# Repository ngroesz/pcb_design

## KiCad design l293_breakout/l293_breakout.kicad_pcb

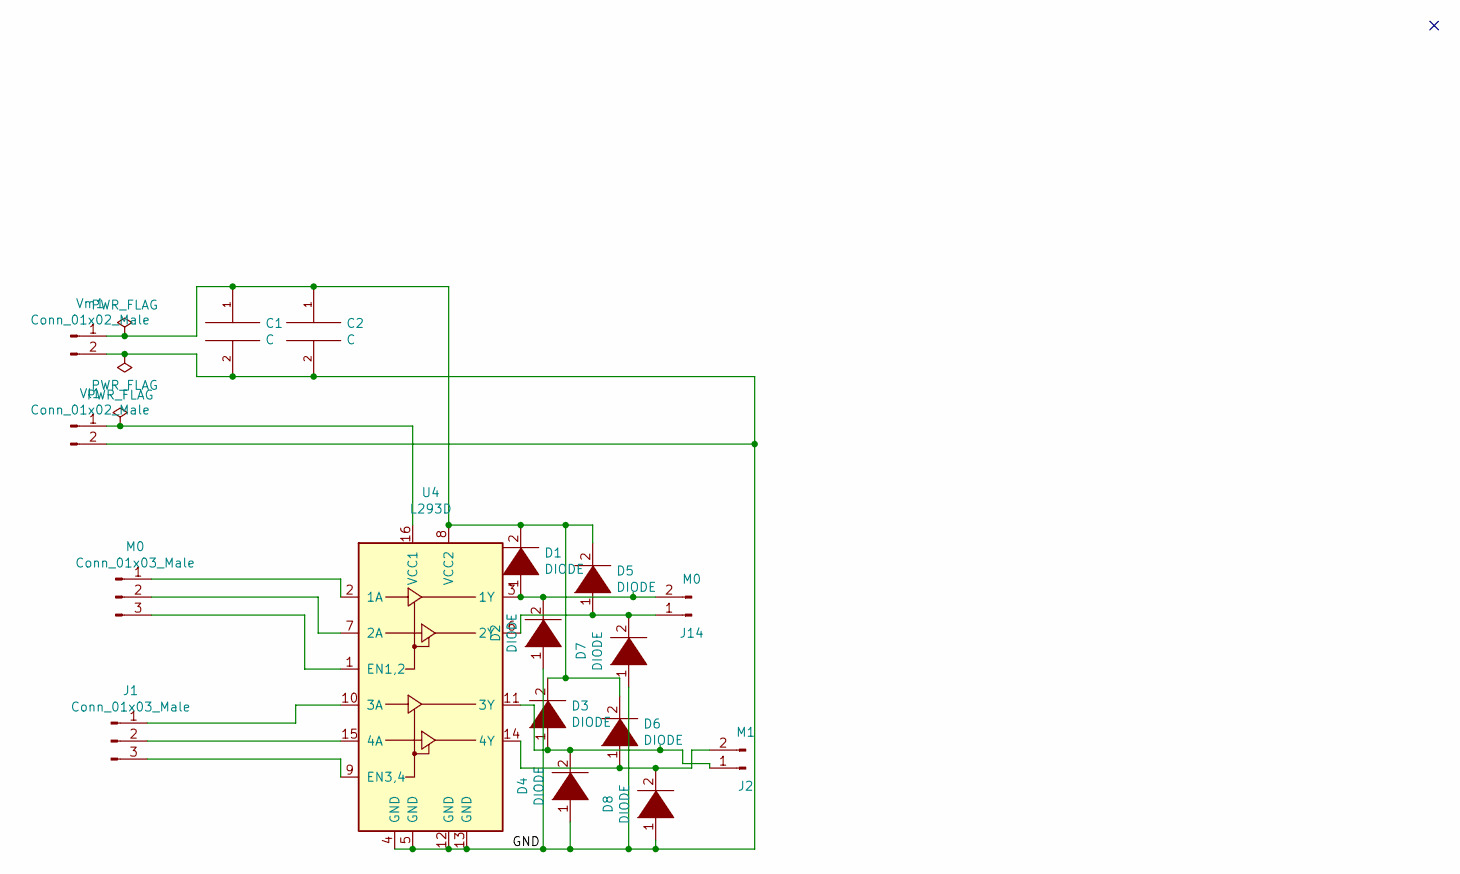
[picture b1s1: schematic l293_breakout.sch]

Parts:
C1: C; C_Disc_D4.7mm_W2.5mm_P5.00mm
C2: C; CP_Radial_D4.0mm_P2.00mm
D1, D2, D3, D4, D5, D6, D7, D8: DIODE; D_A-405_P7.62mm_Horizontal
J1: Conn_01x03_Male; JST_EH_B3B-EH-A_1x03_P2.50mm_Vertical
J2: M1; JST_EH_B2B-EH-A_1x02_P2.50mm_Vertical
J14: M0; JST_EH_B2B-EH-A_1x02_P2.50mm_Vertical
M0: Conn_01x03_Male; JST_EH_B3B-EH-A_1x03_P2.50mm_Vertical
U4: L293D; DIP-16_W7.62mm
Vl1: Conn_01x02_Male; JST_EH_B2B-EH-A_1x02_P2.50mm_Vertical
Vm1: Conn_01x02_Male; JST_EH_B2B-EH-A_1x02_P2.50mm_Vertical

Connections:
/GND: C1.2, C2.2, D2.1 (K), D4.1 (K), D7.1 (K), D8.1 (K), U4.4 (GND), U4.5 (GND), U4.12 (GND), U4.13 (GND), Vl1.2, Vm1.2
unnamed: C1.1, C2.1, D1.2 (A), D3.2 (A), D5.2 (A), D6.2 (A), U4.8 (VCC2), Vm1.1
unnamed: D1.1 (K), D2.2 (A), J14.2, U4.3 (1Y)
unnamed: D3.1 (K), D4.2 (A), J2.1, U4.11 (3Y)
unnamed: D5.1 (K), D7.2 (A), J14.1, U4.6 (2Y)
unnamed: D6.1 (K), D8.2 (A), J2.2, U4.14 (4Y)
unnamed: J1.1, U4.10 (3A)
unnamed: J1.2, U4.15 (4A)
unnamed: J1.3, U4.9 (EN3,4)
unnamed: M0.1, U4.2 (1A)
unnamed: M0.2, U4.7 (2A)
unnamed: M0.3, U4.1 (EN1,2)
unnamed: U4.16 (VCC1), Vl1.1

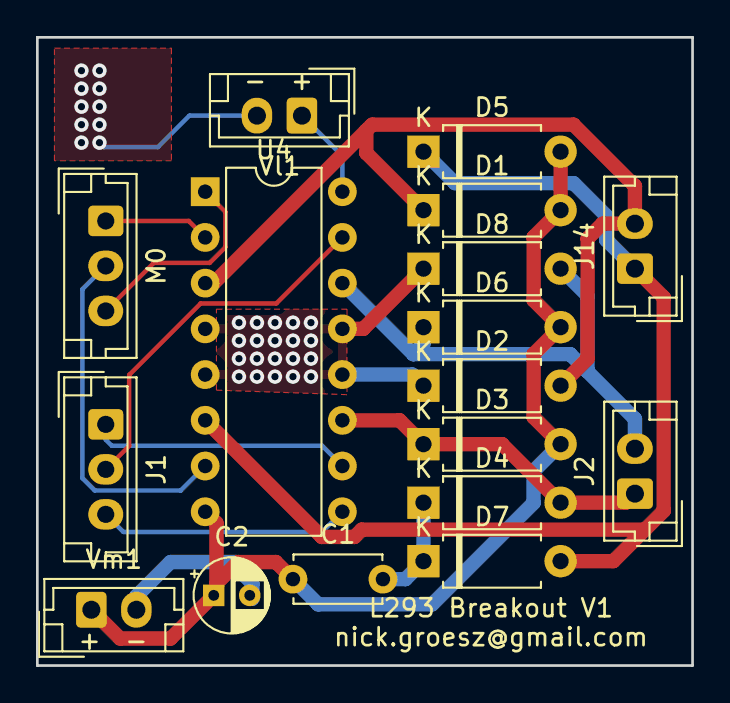
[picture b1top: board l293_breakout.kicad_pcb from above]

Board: 2 copper layers, 36.4 x 34.9 mm, 17 parts (0 on the bottom side), 13 nets.

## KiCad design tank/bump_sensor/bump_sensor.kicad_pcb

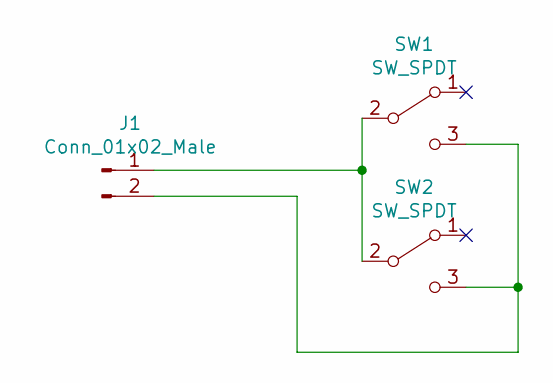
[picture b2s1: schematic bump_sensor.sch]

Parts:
J1: Conn_01x02_Male; JST_EH_B2B-EH-A_1x02_P2.50mm_Vertical
SW1, SW2: SW_SPDT; micro_switch

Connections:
unnamed: J1.1, SW1.2 (B), SW2.2 (B)
unnamed: J1.2, SW1.3 (C), SW2.3 (C)

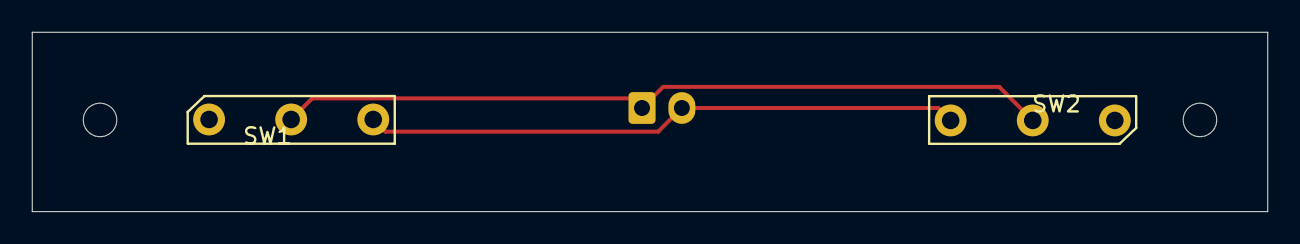
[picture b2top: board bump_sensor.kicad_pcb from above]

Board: 2 copper layers, 77.5 x 11.2 mm, 3 parts (1 on the bottom side), 2 nets.

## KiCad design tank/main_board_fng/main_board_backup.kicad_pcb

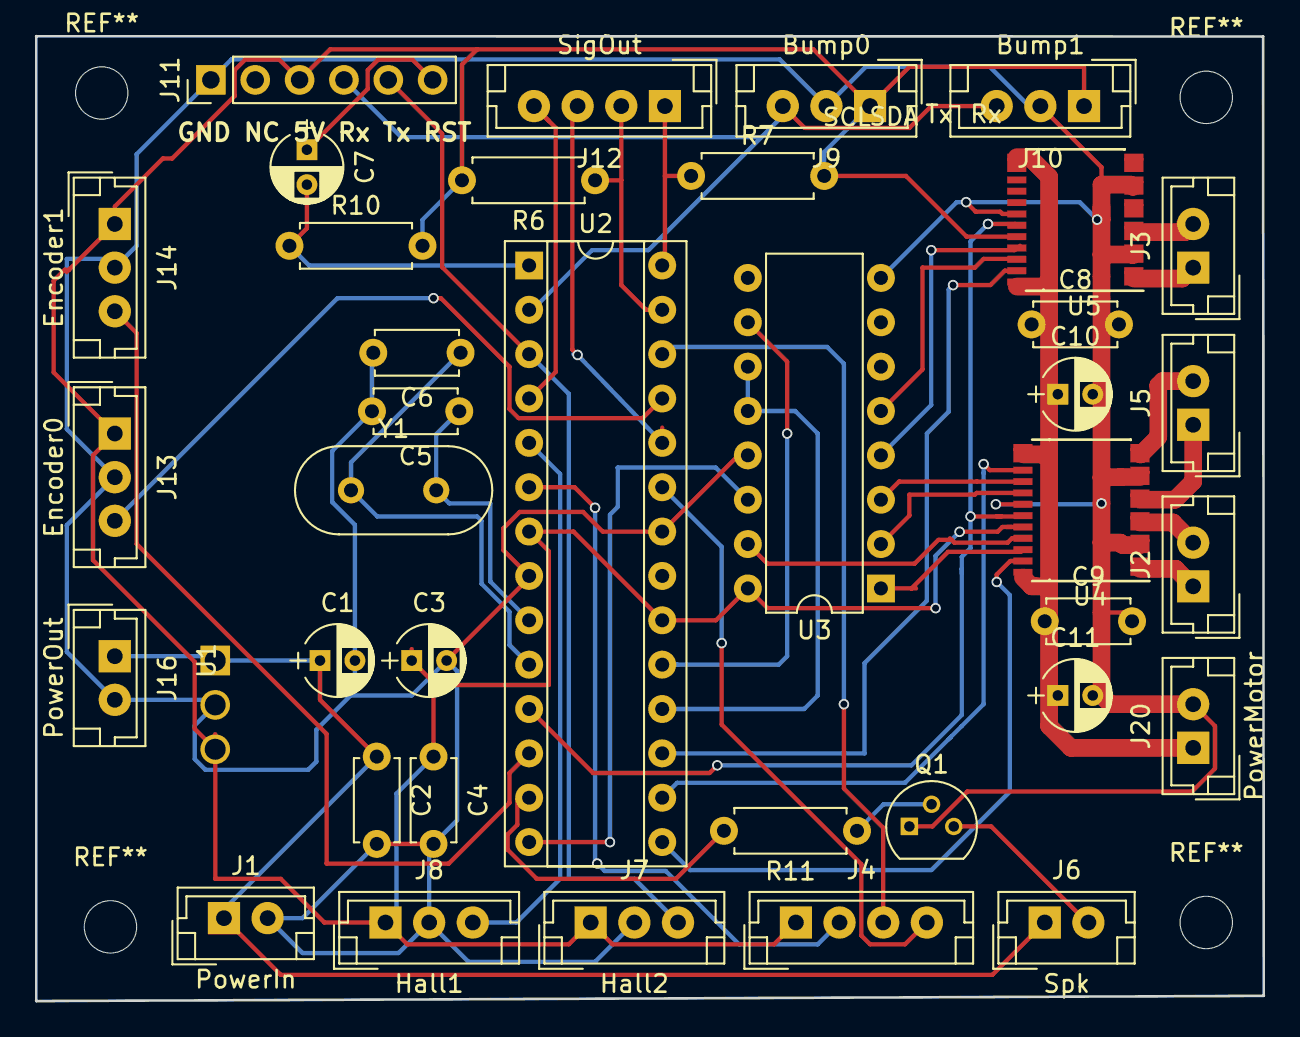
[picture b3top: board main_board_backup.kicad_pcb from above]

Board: 2 copper layers, 70.3 x 55.2 mm, 38 parts (0 on the bottom side), 44 nets.

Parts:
C1: CP1; CP_Radial_D4.0mm_P2.00mm
C2: C2; C_Disc_D4.7mm_W2.5mm_P5.00mm
C3: CP3; CP_Radial_D4.0mm_P2.00mm
C4: C4; C_Disc_D4.7mm_W2.5mm_P5.00mm
C5: C5; C_Disc_D4.7mm_W2.5mm_P5.00mm
C6: C6; C_Disc_D4.7mm_W2.5mm_P5.00mm
C7, C10, C11: CP; CP_Radial_D4.0mm_P2.00mm
C8, C9: C; C_Disc_D4.7mm_W2.5mm_P5.00mm
J1: PowerIn; JST_EH_B02B-EH-A_02x2.50mm_Straight
J2: M1; JST_EH_B02B-EH-A_02x2.50mm_Straight
J3: M2; JST_EH_B02B-EH-A_02x2.50mm_Straight
J4: LEDs; JST_EH_B04B-EH-A_04x2.50mm_Straight
J5: M0; JST_EH_B02B-EH-A_02x2.50mm_Straight
J6: Spk; JST_EH_B02B-EH-A_02x2.50mm_Straight
J7: Hall2; JST_EH_B03B-EH-A_03x2.50mm_Straight
J8: Hall1; JST_EH_B03B-EH-A_03x2.50mm_Straight
J9: Bump0; JST_EH_B03B-EH-A_03x2.50mm_Straight
J10: Bump1; JST_EH_B03B-EH-A_03x2.50mm_Straight
J11: Programming Header; Pin_Header_Straight_1x06_Pitch2.54mm
J12: SigOut; JST_EH_B04B-EH-A_04x2.50mm_Straight
J13: Encoder0; JST_EH_B03B-EH-A_03x2.50mm_Straight
J14: Encoder1; JST_EH_B03B-EH-A_03x2.50mm_Straight
J16: PowerOut; JST_EH_B02B-EH-A_02x2.50mm_Straight
J20: PowerMotor; JST_EH_B02B-EH-A_02x2.50mm_Straight
Q1: 2N3904; TO-92_Molded_Narrow
R6: R6; R_Axial_DIN0207_L6.3mm_D2.5mm_P7.62mm_Horizontal
R7: R7; R_Axial_DIN0207_L6.3mm_D2.5mm_P7.62mm_Horizontal
R10: R10; R_Axial_DIN0207_L6.3mm_D2.5mm_P7.62mm_Horizontal
R11: R11; R_Axial_DIN0207_L6.3mm_D2.5mm_P7.62mm_Horizontal
U1: L7805
U2: ATMEGA328P-PU; DIP-28_W7.62mm_Socket
U3: SN74HC595; DIP-16_W7.62mm
U4, U5: TB6612FNG
Y1: Crystal; Crystal_HC49-U_Vertical

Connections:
4.5V: C3.1, C4.1, J4.1, J7.1, J8.1, J9.1, J10.1, J11.3, J13.1, J14.1, R6.2, R7.2, R10.2, U1.3, U2.7, U2.20, U3.16, U4.20, U5.20
9V: C1.1, C2.1, J1.1, J6.1, J16.1, U1.1
Bump: J9.3, J10.3, J11.4, U2.2
Encoder0: J13.3, U2.25
Encoder1: J14.3, U2.12
GND: C1.2, C2.2, C3.2, C4.2, C5.2, C6.2, C8.2, C9.2, C10.2, C11.2, J1.2, J7.2, J8.2, J9.2, J10.2, J11.1, J13.2, J14.2, J16.2, J20.2, Q1.1, U1.2, U2.8, U2.22, U3.8, U3.13, U4.3, U4.4, U4.9, U4.10, U4.18, U5.3, U5.4, U5.9, U5.10, U5.18
IRRx: J12.4, U2.4
IRTx: J12.3, U2.24
LED0: J4.2, U2.6
LED1: J4.3, U2.26
LED2: J4.4, U2.23
M0+: U3.15, U4.21
M0-: U3.1, U4.22
M0PWM: U2.15, U4.23
M1+: U3.2, U4.17
M1-: U3.3, U4.16
M1PWM: U2.16, U4.15
M2+: U3.4, U5.21
M2-: U3.5, U5.22
M2PWM: U2.17, U5.23
MEnable: U2.11, U4.19, U5.19
unnamed: C5.1, U2.9, Y1.2
unnamed: C6.1, U2.10, Y1.1
unnamed: C7.1, J11.6
unnamed: C7.2, R10.1, U2.1
unnamed: J2.1, U4.1, U4.2
unnamed: J2.2, U4.5, U4.6
unnamed: J3.1, U5.1, U5.2
unnamed: J3.2, U5.5, U5.6
unnamed: J5.1, U4.7, U4.8
unnamed: J5.2, U4.11, U4.12
unnamed: J6.2, Q1.3
unnamed: Q1.2, R11.1
unnamed: U5.7, U5.8
unnamed: U5.11, U5.12
SCL: J12.1, R7.1, U2.28
SDA: J12.2, R6.1, U2.27
SER: U2.14, U3.14
SPK: R11.2, U2.13
SRCLK: U2.18, U3.11, U3.12
SRCLR: U2.19, U3.10
TurretCal: J7.3, J11.5, U2.3
TurretEncoder: J8.3, U2.5
Vm: C8.1, C9.1, C10.1, C11.1, J20.1, U4.13, U4.14, U4.24, U5.13, U5.14, U5.24

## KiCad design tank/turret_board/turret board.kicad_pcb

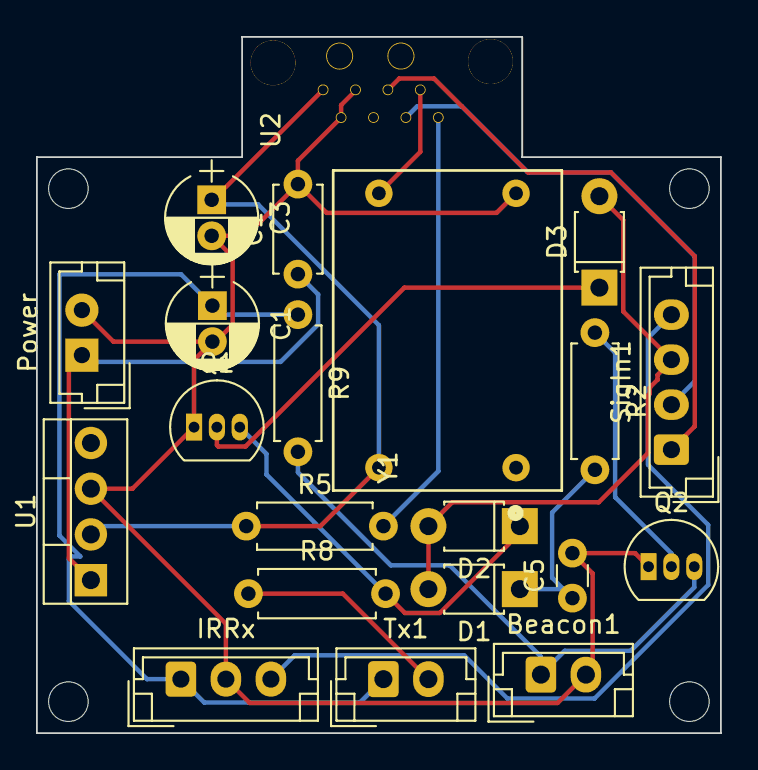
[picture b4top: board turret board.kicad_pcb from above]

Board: 2 copper layers, 38.0 x 38.7 mm, 21 parts (0 on the bottom side), 16 nets.

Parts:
Beacon1: CONN_01X02; JST_EH_B2B-EH-A_1x02_P2.50mm_Vertical
C1, C3: CP; CP_Radial_D5.0mm_P2.00mm
C1#2: C_Small; C_Disc_D4.7mm_W2.5mm_P5.00mm
C5: C; C_Disc_D3.0mm_W1.6mm_P2.50mm
D1, D2, D3: D; D_T-1_P5.08mm_Horizontal
IRRx: CONN_01X03; JST_EH_B3B-EH-A_1x03_P2.50mm_Vertical
Power: Conn_01x02_Male; JST_EH_B02B-EH-A_02x2.50mm_Straight
Q1, Q2: 2N3904; TO-92_Inline_Narrow_Oval
R2, R5, R8, R9: R; R_Axial_DIN0207_L6.3mm_D2.5mm_P7.62mm_Horizontal
SigIn1: CONN_01X04; JST_EH_B4B-EH-A_1x04_P2.50mm_Vertical
Tx1: TX; JST_EH_B2B-EH-A_1x02_P2.50mm_Vertical
U1: KA378R33; TO-220-4_Vertical
U2: pixart_ir
Y1: Crystal_4pin; ECS-100AX

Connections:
3.3V: C3.1, R5.1, U1.2, U2.1, Y1.14
5V: C1.1, IRRx.1, R9.1, Tx1.1
Beacon: Beacon1.1, Q2.3, R9.2
GND: Beacon1.2, C1.2, C1#2.2, C3.2, C5.2, IRRx.2, Power.2, Q1.1, Q2.1, U1.3, U2.2, U2.3, Y1.7
IRRx: IRRx.3, SigIn1.4
IRSig: D1.2, D2.2, D3.2, SigIn1.3
IRTx: R8.1, Tx1.2
unnamed: C1#2.1, Power.1, U1.1
unnamed: C5.1, D1.1, R2.2
unnamed: D2.1, Q1.3, R8.2
unnamed: D3.1, Q1.2
unnamed: Q2.2, R2.1
unnamed: U2.7, Y1.8
RESET: R5.2, U2.8
SDA: SigIn1.2, U2.6
SLC: SigIn1.1, U2.5
